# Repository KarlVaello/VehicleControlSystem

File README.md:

# Vehicle Control System

### What is VCS?
In modern vehicles almost 80% of the vehicle is controlled electronically. That's just VCS, a control system. Focused on electric vehicles but can be easily modified for other types.
VCS consists of several units and modules, all connected by an area network bus, based on rs-485 and my own [data protocol](https://github.com/KarlVaello/VCS/wiki/Unit-Communication-protocol), allowing modularization.
In this project you will find both the hardware and the software of each unit or module.

 Electronic control units / modules
 
UNITS:
- CCU Central Control Unit
	- CCU Cluster Control Unit
	- CCU Central Control Unit
- EmCU Electric-motor Control Unit
- BCU Battery Control Unit

MODULES:
- CcCM Central-console Control Module
- SteeringWheel Control Module
- BCM Body Control Module
- BlCM Back-lights Control Module
- FlCM Front-lights Control Module

### SCREENSHOTS

BASE MODULE

# Full Documentation

See the [WIKI](https://github.com/KarlVaello/VCS/wiki) for full documentation, examples, operational details and other information.

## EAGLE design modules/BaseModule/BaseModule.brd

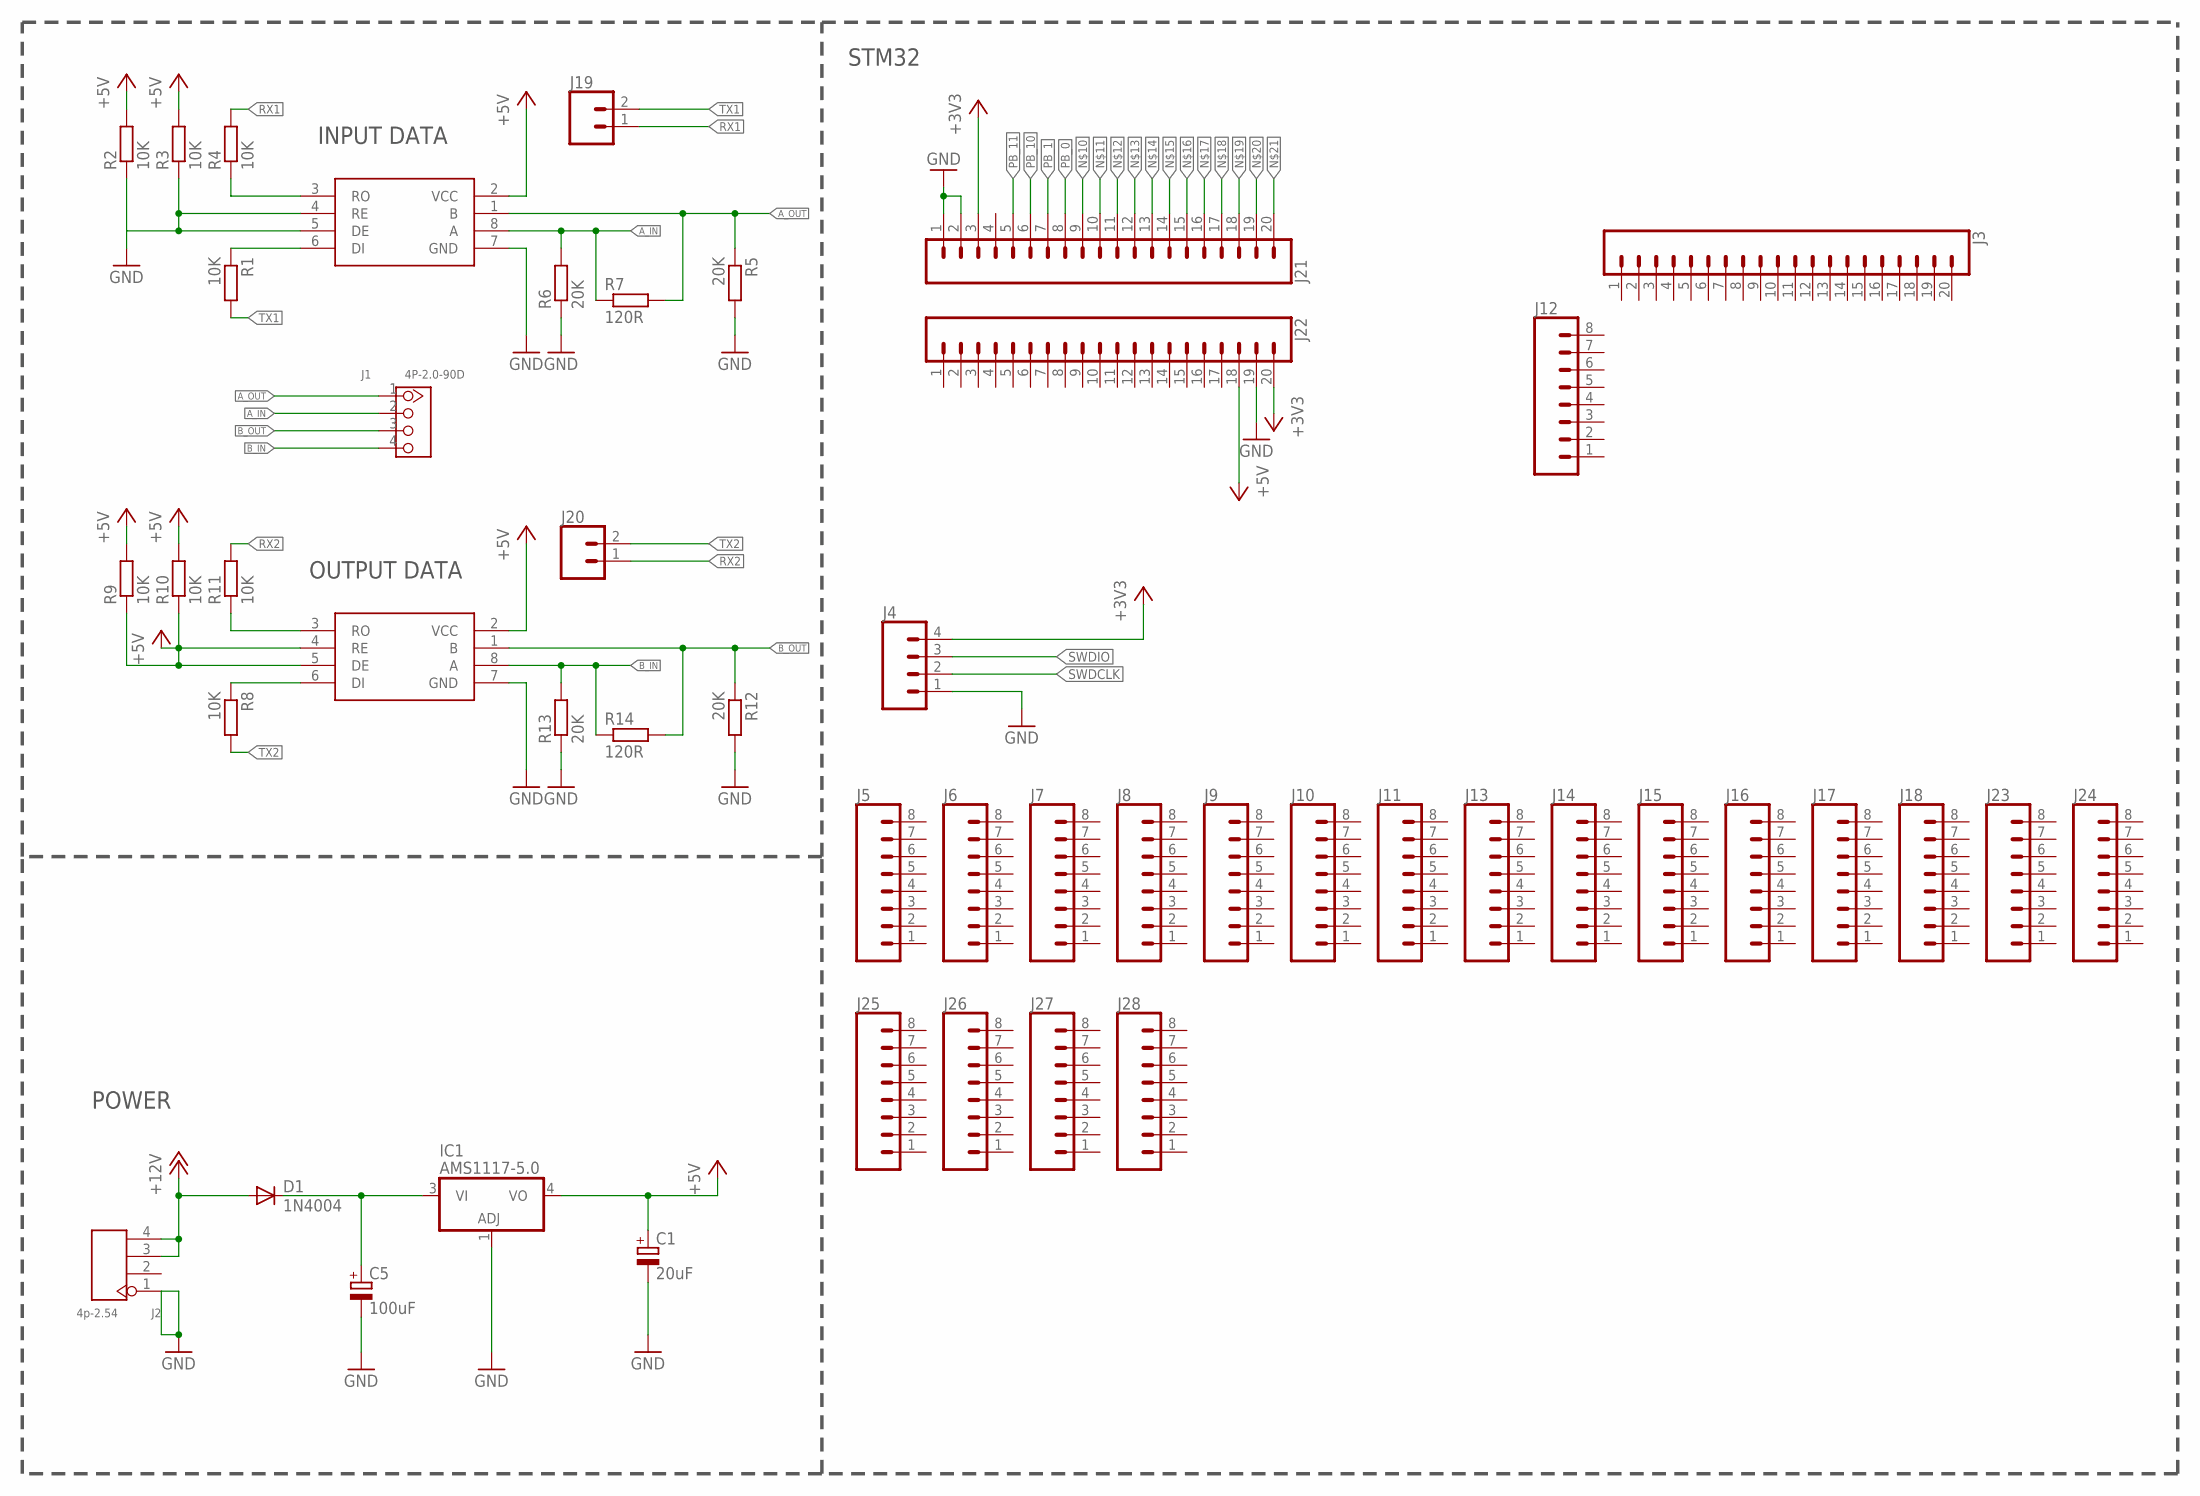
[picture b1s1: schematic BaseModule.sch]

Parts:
C1: 20uF; 153CLV-0405
C5: 100uF; 153CLV-0405
D1: 1N4004; DO41-10
IC1: AMS1117-5.0; SOT223
J1: 4P-2.0-90D; HW4-2.0-90D
J2: 4p-2.54; H4-2.54
J3, J21, J22: CONN_20; 1X20
J4: CONN_04; 1X04
J5, J6, J7, J8, J9, J10, J11, J12, J13, J14, J15, J16, J17, J18, J23, J24, J25, J26, J27, J28: CONN_08"; 1X08
J19, J20: CONN_02; 1X02
R1, R2, R3, R4, R8, R9, R10, R11: 10K; R0603
R5, R6, R12, R13: 20K; R0603
R7, R14: 120R; R0603
U$1, U$2: MAX485

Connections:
+3V3: J4.4, J21.3, J22.20
+5V: C1.+, IC1.4 (VO), J22.18, R2.2, R3.2, R9.1, R9.2, R10.1, R10.2, U$1.2 (VCC), U$2.2 (VCC), U$2.4 (RE), U$2.5 (DE)
+12V: D1.A, J2.3, J2.4
A_IN: J1.2, R6.2, R7.1, U$1.8 (A)
A_OUT: J1.1, R5.1, R7.2, U$1.1 (B)
B_IN: J1.4, R13.2, R14.1, U$2.8 (A)
B_OUT: J1.3, R12.1, R14.2, U$2.1 (B)
GND: C1.-, C5.-, IC1.1 (ADJ), J2.1, J4.1, J21.1, J21.2, J22.19, R2.1, R3.1, R5.2, R6.1, R12.2, R13.1, U$1.4 (RE), U$1.5 (DE), U$1.7 (GND), U$2.7 (GND)
unnamed: R4.1, U$1.3 (RO)
unnamed: R11.1, U$2.3 (RO)
unnamed: R8.1, U$2.6 (DI)
unnamed: R1.1, U$1.6 (DI)
unnamed: C5.+, D1.C, IC1.3 (VI)
PB_0: J21.8
PB_1: J21.7
PB_10: J21.6
PB_11: J21.5
RX1: J19.1, R4.2
RX2: J20.1, R11.2
SWDCLK: J4.2
SWDIO: J4.3
TX1: J19.2, R1.2
TX2: J20.2, R8.2

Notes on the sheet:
INPUT DATA
OUTPUT DATA
POWER
STM32

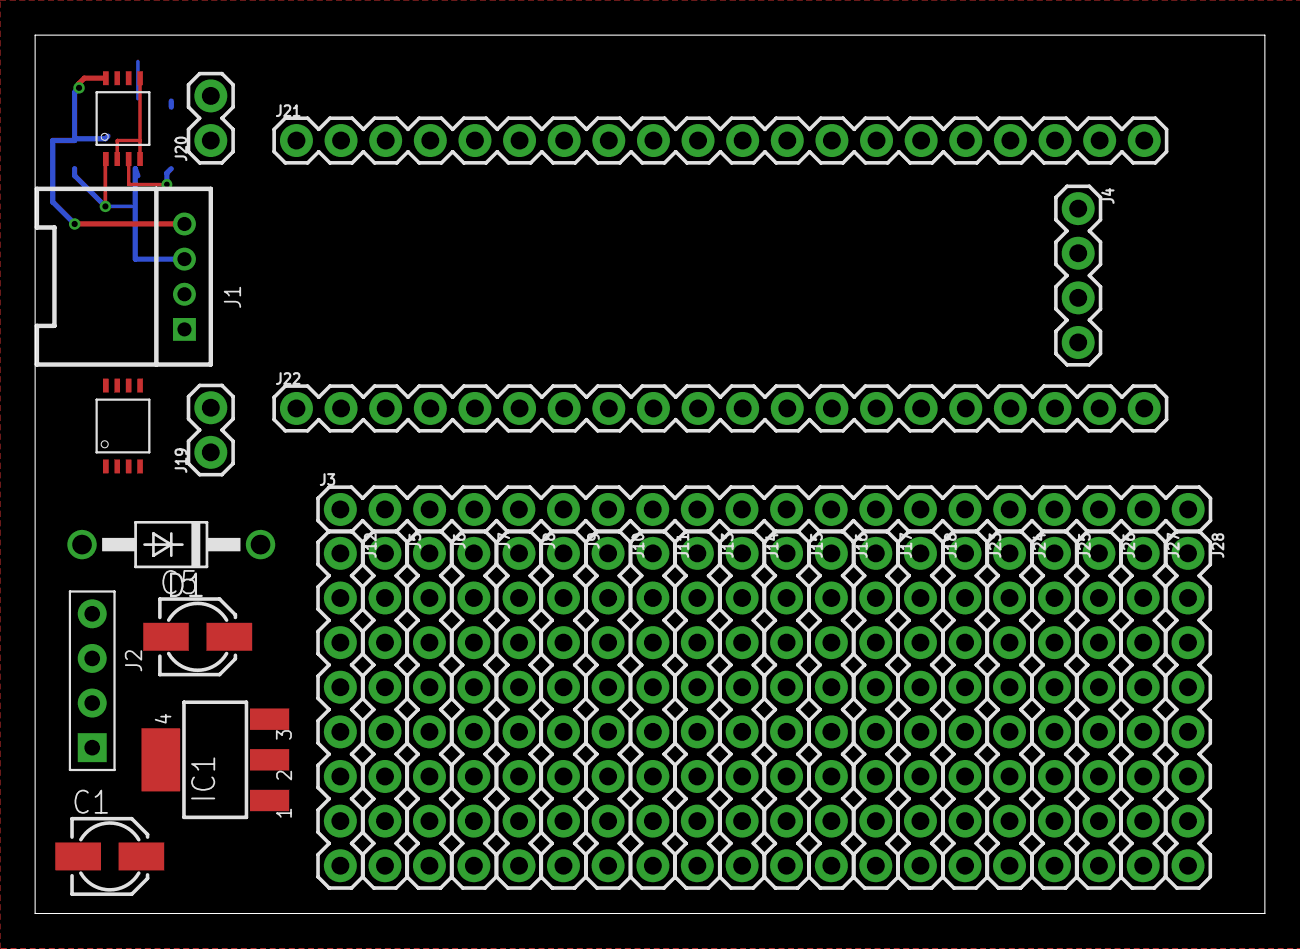
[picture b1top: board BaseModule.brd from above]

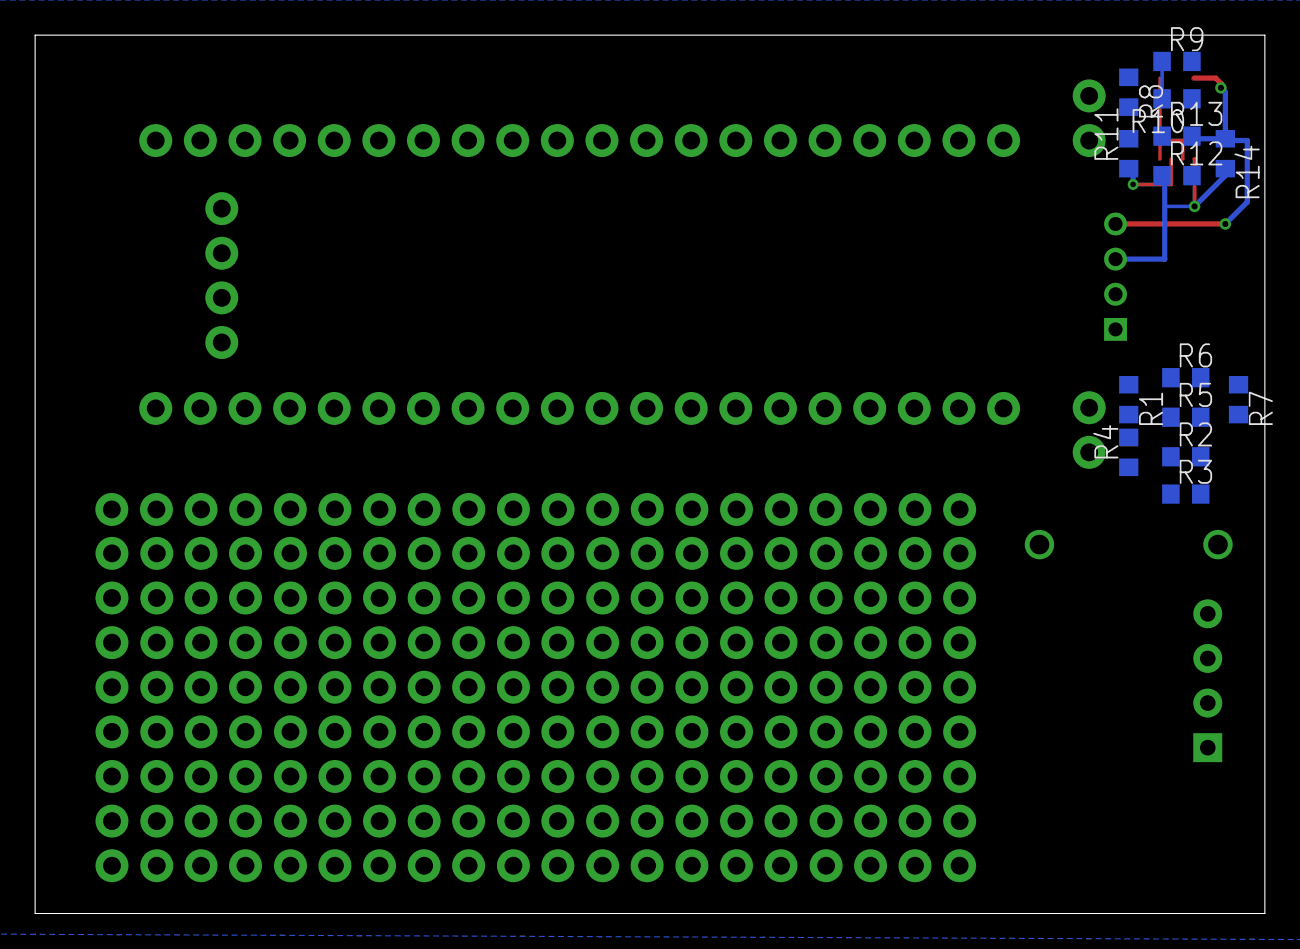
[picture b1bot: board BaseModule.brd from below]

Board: 2 copper layers, 70.0 x 50.0 mm, 48 parts (14 on the bottom side), 17 nets.

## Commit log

2017-02-07 Initial commit
    Initial commit
2017-02-08 Basic Serial Implementation
    Basic Serial Implementation
2017-02-08 Migrated widgets to new display widget system
    Migrated all widget to paintEvent and QpainterS
    Added new errorIcon.
    Corrected speedPinter display
2017-02-08 Serial communication updates
    Serial communication updates
2017-02-09 More paintEvent migration
    More paintEvent migration
2017-02-10 Font, serial and qprinter modifications
    Font, serial and qprinter modifications
2017-02-10 New Screen size (pixels)
    New Screen size (pixels)
2017-02-15 New Fonts
2017-02-16 readme file, new serial class (UpdateSerial.py)
2017-02-16 readme update
2017-02-16 readme updates
2017-02-17 more readme updates
2017-02-17 Update README.md
    More readme updates
2017-02-17 Folders modifications
    Folders, descriptions modifications to add Order to Project
2017-02-17 Adding more project info
    Adding more project info
2017-02-17 More info, files ranaming
    More info, files ranaming
2017-02-17 more info
2017-02-20 new classes
2017-02-20 new classes files
2017-02-20 New SVG files
    New SVG files to get better rendering UI
2017-02-20 New angle correction speedPointer
    New angle correction speedPointer
2017-02-20 Added test sounds
    Added test sounds
2017-02-21 try to add some sound
2017-02-21 New Cluster Display size 1280x720 to fit SHARP TFT-LCD LQ123K1LG03
2017-02-21 Minor changes
2017-02-21 Minor changes. Wiring diagram update
    Minor changes. Wiring diagram update
2017-02-22 New Icon to test Qthread
2017-02-23 Graphics update
    Graphics update
2017-02-23 minus modifications
2017-02-23 Minimal changes + Screenshot
    Minimal changes + Screenshot
2017-02-24 Icongs and more screenshots
    Icongs and more screenshots
2017-02-24 Set theme jekyll-theme-dinky
2017-02-24 Set theme jekyll-theme-slate
2017-02-25 New TODO file
2017-02-25 WiringDiagram.xml
2017-02-25 WiringDiagram.png
2017-02-25 Wiring diagram update
    Wiring diagram update
2017-02-26 Update WiringDiagram
2017-02-26 new wiringdiagram
2017-02-26 New EmCU folder and KiCad projecto
    New EmCU folder and KiCad projecto
2017-02-27 STM32 Documentation. STM32 Core board update
2017-03-01 Graphics update
2017-03-10 Cluster display info docs
2017-03-20 graphic update
2017-03-20 folders mooving and renamings
2017-03-20 Update to QT c++ project
    Update to QT c++ project to get better performance
2017-03-21 Link img files by resources on QT
2017-03-21 minimal updates
2017-03-22 Starting to implement notification systema
2017-03-22 notifications updates
2017-03-23 Notifications works
    Basic notifications works
    NotificationInfo
    NotificationManager
    NotificationWidget
    NotificationWidgetManage
2017-03-24 notification updates
2017-04-04 New Classes to communicate between units
    New UnitCommunication class, data exchange.
    New Infotainment class, data holder.
    More info on the wiki.
    cameraCaptureBuffer and cameraSteam are new too but there are on a
    standby because it’s need a specific hardware (camera) selection to
    continue develop it. The hardware determines almost all code work.
2017-04-04 Unit Communication diagram
2017-04-04 minimal update
2017-04-04 min updates
2017-04-04 data infotaiment updates
2017-04-05 update smooth speed pointer rotation
2017-04-05 debug communication error
2017-04-05 unitCommunication optimization routines and varaibles
2017-04-18 RS485 network on receiving data working perfect
2017-05-13 folders reorganized, arduino stm32 code rs-485 for test communications
2017-05-16 unit communication updates
2017-05-19 communication updates
2017-05-24 DB9 connector
2017-05-24 DB9_SINGLE connector
2017-05-25 DB9_single updated
2017-05-25 new db9 single stl
2017-06-27 Added Base module
    Added Base Module as de base circuit of every module with stm32
    microcontroller
2017-06-28 BaseBoard updates + hardware documentation
2017-07-07 base module update
    base module update
2017-07-07 gitignore
    gitignore
2017-07-07 UnitCommunication updates
    UnitCommunication updates
2017-07-10 unitCommunication_diagram Update
2017-07-16 unitCommunication Updates
    Now unitCommunication just hold diferente communication (propulsion,
    confort…). Even different communication had their own new class. The
    just manage their own communication and in different threats.
2017-07-16 documentation and base module updates
2017-07-17 Documentation update
2017-07-19 Updates unitPropulsionCom + graphics
    unitPropulsionCommunication works perfect right now tested with modules
    as emitters.
2017-08-02 BaseModule pcb updates
2017-09-13 Minimal updates on cluster.cpp
2017-09-13 Updates on .pro user settings
2017-09-13 Rename notificationmanager.h to notificationManager.h
2017-09-13 Rename notificationinfo.cpp to notificationInfo.cpp
2017-09-13 Rename notificationinfo.h to notificationInfo.h
2017-09-13 Rename notificationmanager.cpp to notificationManager.cpp
2017-09-13 Rename notificationwidget.cpp to notificationWidget.cpp
2017-09-13 Rename notificationwidget.h to notificationWidget.h
2017-09-14 Project clean for Linux
2017-09-14 Add font
2017-10-24 BaseModule updates (new board)
    Made with kicad
2017-10-26 BaseModule updates and documentation updates
2017-10-27 BaseModule ScreenShoot update

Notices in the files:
parts and their libraries:
SparkFun-Connectors: Licensing: Creative Commons ShareAlike 4.0 International - https://creativecommons.org/licenses/by-sa/4.0
